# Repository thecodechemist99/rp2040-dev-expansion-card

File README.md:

# Dual RP2040 Expansian Card for Framework Laptop

This extension card includes two RP2040 microcontrollers and can be used as an internal
development board as well as external debugger for other RP2040-bsed boards (e.g. Raspberry
Pi Pico) or even entirely diffrent architectures.

## License

Expansion Card © 2024 by Florian Beck is licensed under CC BY 4.0.
Based on a reference design by Framework Computer Inc, licensed under CC BY 4.0, which can
be found [here](https://github.com/FrameworkComputer/ExpansionCards).
To view a copy of this license, visit http://creativecommons.org/licenses/by/4.0/

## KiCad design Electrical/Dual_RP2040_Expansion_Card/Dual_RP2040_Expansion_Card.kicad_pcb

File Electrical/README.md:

# Expansion Card Electrical CAD

This section contains the KiCad design files for the board.

## License

Expansion Card © 2024 by Florian Beck is licensed under CC BY 4.0.
Based on a reference design by Framework Computer Inc, licensed under CC BY 4.0, which can
be found [here](https://github.com/FrameworkComputer/ExpansionCards).
To view a copy of this license, visit http://creativecommons.org/licenses/by/4.0/

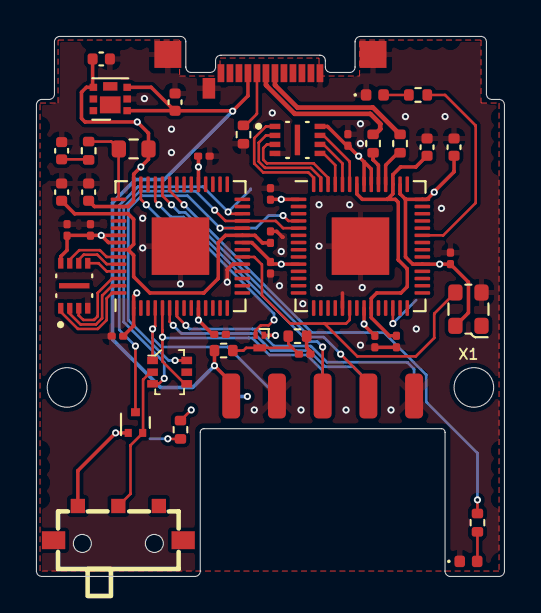
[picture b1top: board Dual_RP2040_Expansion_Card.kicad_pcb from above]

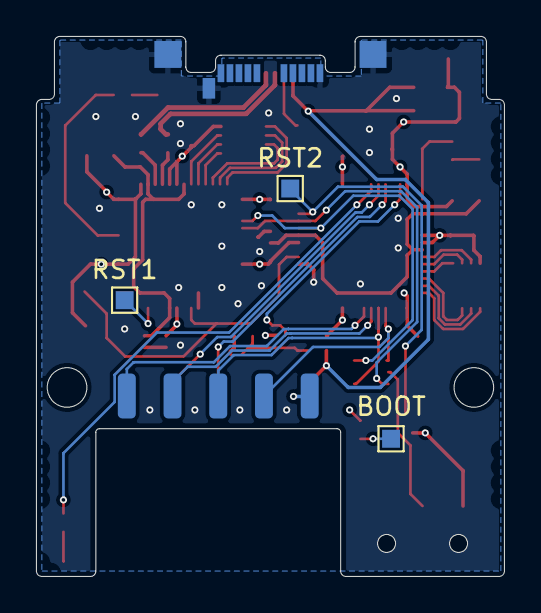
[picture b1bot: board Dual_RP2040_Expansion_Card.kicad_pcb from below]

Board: 4 copper layers, 26.0 x 30.0 mm, 53 parts (5 on the bottom side), 43 nets.

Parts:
C1, C2: 10u; C_0402_1005Metric
C5, C6, C10, C11, C12, C13, C16, C19, C20, C21, C22, C24: 100n; C_0201_0603Metric
C7, C8, C9, C14, C15: 2u2; C_0402_1005Metric
C18: 1n; C_0201_0603Metric
D1: Green; LED_0402_1005Metric
D2: Orange; LED_0402_1005Metric
H1, H2: MountingHole; MountingHole_2.2mm_M2
J1: Conn 10P; Pinheader_PCB_Edge_2x5_2.54mm
P1: USB_C_Plug_USB2.0; USB_C_Plug_Molex_105444
Q1: DMG1012T; Diodes_DFN1006-3
Q2: Q_PMOS_SGD; SOT-723
Q3: Q_Dual_NPN_NPN_C2E2C1E1B1B2; SOT-363
R1: 5k1; R_0402_1005Metric
R2: 1K; R_0402_1005Metric
R4, R17: 470R; R_0402_1005Metric
R9, R10: 27R; R_0402_1005Metric
R11: 200R; R_0603_1608Metric
R12: 1R; R_0402_1005Metric
R15: 200K; R_0402_1005Metric
R16: 100K; R_0402_1005Metric
S1: K3-1203S-E1; SW-SMD_K3-1203S-E1
TP1, TP2, TP3, TP4: TestPoint; TestPoint_Pad_1.5x1.5mm
TP5: BOOT; TestPoint_Pad_1.0x1.0mm
TP7: RST2; TestPoint_Pad_1.0x1.0mm
TP8: RST1; TestPoint_Pad_1.0x1.0mm
U1: AP7366EA-3.3; Diodes_UDFN2020-6_Type-F
U2, U4: RP2040; QFN-56-1EP_7x7mm_P0.4mm_EP3.2x3.2mm
U3, U5: W25Q16JVUXIQ; IC_W25Q16JVUXIQ_TR
X1: SX2M12.000M20F30TNN; Oscillator_SMD_ECS_2520MV-xxx-xx-4Pin_2.5x2.0mm

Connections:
+3V3: C2.1, C6.1, C8.1, C10.1, C11.1, C13.1, C15.1, C16.1, C19.1, C20.1, C21.1, C22.1, C24.1, J1.2, Q1.1 (G), Q2.1 (S), R2.2, R11.1, S1.1, U1.4 (VOUT), U2.1 (IOVDD), U2.10 (IOVDD), U2.22 (IOVDD), U2.33 (IOVDD), U2.42 (IOVDD), U2.44 (VREG_IN), U2.48 (USB_VDD), U2.49 (IOVDD), U3.8 (VCC), U4.1 (IOVDD), U4.10 (IOVDD), U4.22 (IOVDD), U4.33 (IOVDD), U4.42 (IOVDD), U4.44 (VREG_IN), U4.48 (USB_VDD), U4.49 (IOVDD), U5.8 (VCC), X1.4 (VDD)
/Debug Probe Section/1V1_CORE: C12.1, C14.1, U4.23 (DVDD), U4.45 (VREG_VOUT), U4.50 (DVDD)
/Debug Probe Section/LED_INT_EN: R17.1, U4.37 (GPIO25)
/Debug Probe Section/QSPI_SCLK: U4.52 (QSPI_SCLK), U5.6 (CLK)
/Debug Probe Section/QSPI_SD0: U4.53 (QSPI_SD0), U5.5 (DI/IO0)
/Debug Probe Section/QSPI_SD1: U4.55 (QSPI_SD1), U5.2 (DO/IO1)
/Debug Probe Section/QSPI_SD2: U4.54 (QSPI_SD2), U5.3 (~WP/IO2)
/Debug Probe Section/QSPI_SD3: U4.51 (QSPI_SD3), U5.7 (~HOLD/~RESET/IO3)
/Debug Probe Section/QSPI_SS: U4.56 (QSPI_SS), U5.1 (~CS)
/Development Board Section/1V1_CORE: C5.1, C7.1, U2.23 (DVDD), U2.45 (VREG_VOUT), U2.50 (DVDD)
/Development Board Section/ADC_VREF: R11.2, R12.1, U2.43 (ADC_AVDD)
/Development Board Section/GPIO_ADC3: Q1.2 (S), U2.41 (GPIO29_ADC3)
/Development Board Section/QSPI_SCLK: U2.52 (QSPI_SCLK), U3.6 (CLK)
/Development Board Section/QSPI_SD0: U2.53 (QSPI_SD0), U3.5 (DI/IO0)
/Development Board Section/QSPI_SD1: U2.55 (QSPI_SD1), U3.2 (DO/IO1)
/Development Board Section/QSPI_SD2: U2.54 (QSPI_SD2), U3.3 (~WP/IO2)
/Development Board Section/QSPI_SD3: U2.51 (QSPI_SD3), U3.7 (~HOLD/~RESET/IO3)
/Development Board Section/QSPI_SS: U2.56 (QSPI_SS), U3.1 (~CS)
/Development Board Section/RUN: Q2.3 (D), TP7.1, U2.26 (RUN)
DEV_ENABLE: Q2.2 (G), Q3.2 (B1), Q3.5 (B2), S1.2
GND: C1.2, C2.2, C5.2, C6.2, C7.2, C8.2, C9.2, C10.2, C11.2, C12.2, C13.2, C14.2, C15.2, C16.2, C18.2, C19.2, C20.2, C21.2, C22.2, C24.2, D1.1 (K), D2.1 (K), J1.3, J1.9, P1.A1 (GND), P1.A12 (GND), P1.B1 (GND), P1.B12 (GND), P1.S1 (SHIELD), R1.2, R16.2, TP1.1, TP2.1, TP3.1, TP4.1, U1.2 (GND), U2.19 (TESTEN), U2.57 (GND), U3.4 (GND), U4.19 (TESTEN), U4.57 (GND), U5.4 (GND), X1.2 (GND)
GPIO2: J1.4, Q3.1 (E1), U2.4 (GPIO2)
GPIO3: J1.6, Q3.4 (E2), U2.5 (GPIO3)
GPIO4: J1.8, U2.6 (GPIO4)
GPIO5: J1.10, U2.7 (GPIO5)
GPIO_ADC0: J1.7, U2.38 (GPIO26_ADC0)
GPIO_ADC1: J1.5, U2.39 (GPIO27_ADC1)
LED_EN: R4.1, U2.37 (GPIO25)
unnamed: C9.1, R12.2
unnamed: D1.2 (A), R4.2
unnamed: D2.2 (A), R17.2
unnamed: P1.A5 (CC), R1.1
unnamed: C18.1, Q1.3 (D), R15.2, R16.1
unnamed: R2.1, TP5.1
unnamed: TP8.1, U4.26 (RUN)
unnamed: R10.2, U4.46 (USB_DM)
unnamed: R9.2, U4.47 (USB_DP)
OSC_OUT: U2.20 (XIN), U4.20 (XIN), X1.3 (OUT)
SWCLK: Q3.6 (C1), U2.24 (SWCLK), U4.4 (GPIO2)
SWDIO: Q3.3 (C2), U2.25 (SWD), U4.5 (GPIO3)
USB_D_N: P1.A7 (D-), R10.1
USB_D_P: P1.A6 (D+), R9.1
VBUS: C1.1, J1.1, P1.A4 (VBUS), P1.A9 (VBUS), P1.B4 (VBUS), P1.B9 (VBUS), R15.1, U1.1 (EN), U1.3 (VIN)

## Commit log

2024-04-02 First rough draft
2024-04-02 Main layout of chip sections finished
2024-04-03 Current state before flash footprint update
2024-04-03 First complete version
2024-04-04 Current state
2024-04-09 All footprints placed single-sided
2024-04-09 Single layer basic layout finished
2024-04-09 Added edge pin connector
2024-04-10 Layout finished
2024-04-10 Resized components to 0402 minimum
2024-04-10 Latest state
2024-04-10 Added test points
2024-04-10 Production design v1 finished
2024-04-11 Fixed missing drill holes for switch
2024-06-22 Exclude zip archives
2024-06-22 Removed obsolete files
2024-06-22 Renamed files
2024-06-22 Removed old project file
2024-06-22 Ignore MacOS system files

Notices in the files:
Electrical/Dual_RP2040_Expansion_Card/Dual_RP2040_Expansion_Card.kicad_pcb:
This work is licensed under a Creative Commons Attribution 4.0 International License
